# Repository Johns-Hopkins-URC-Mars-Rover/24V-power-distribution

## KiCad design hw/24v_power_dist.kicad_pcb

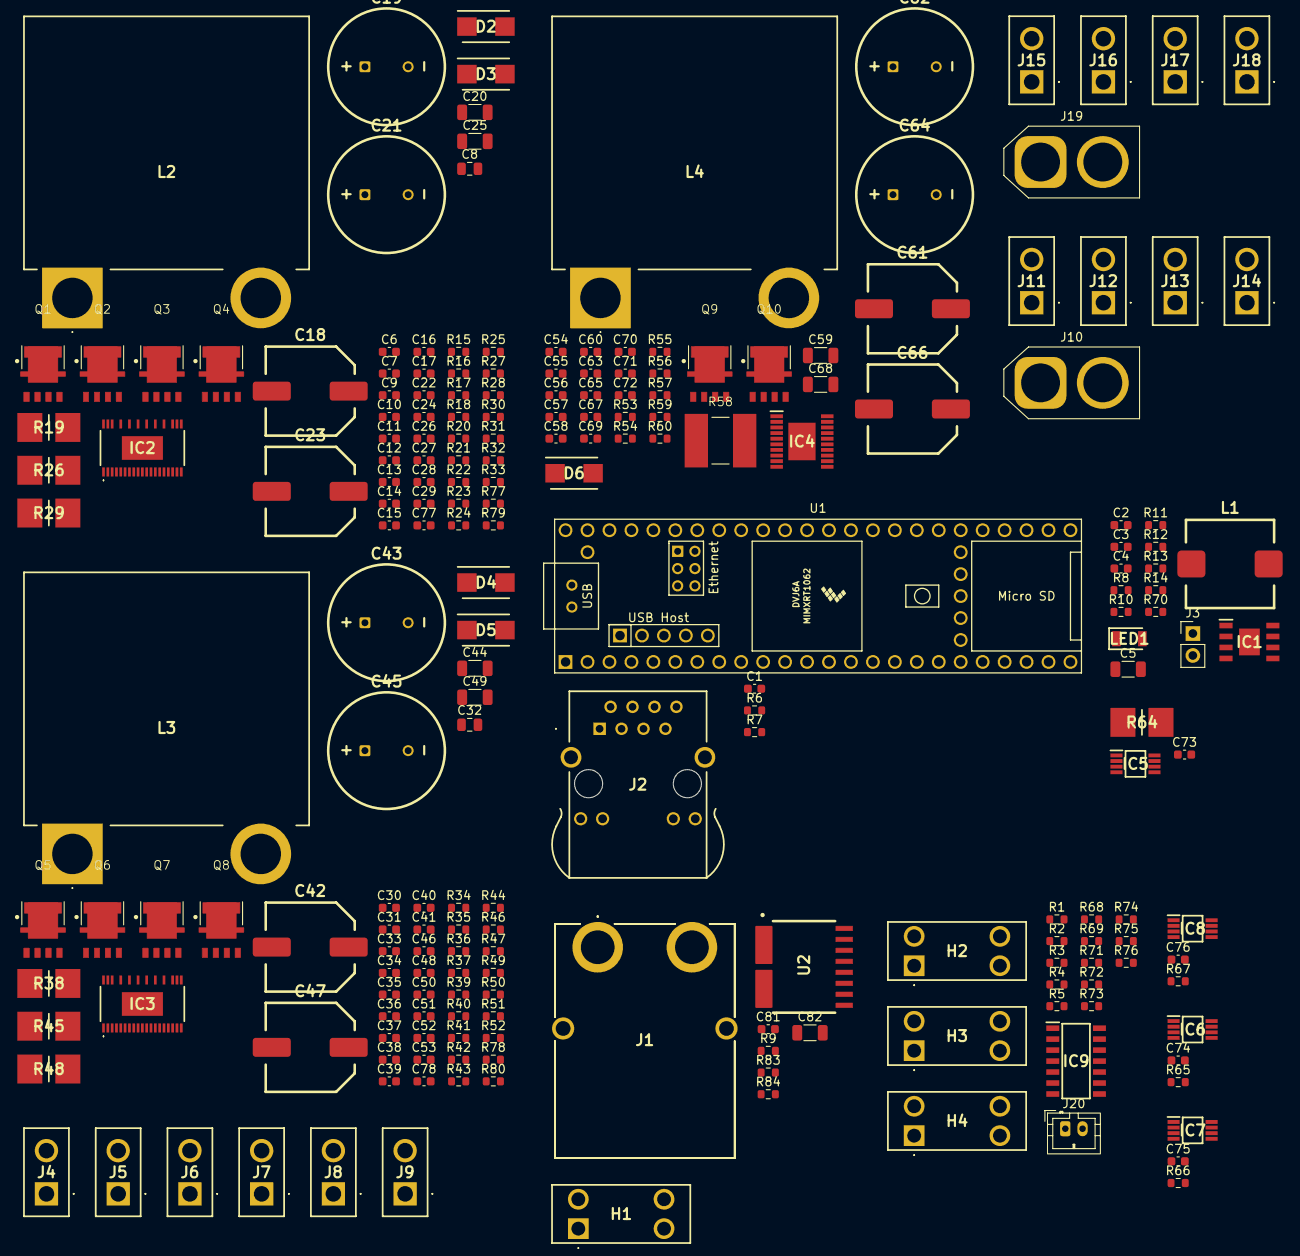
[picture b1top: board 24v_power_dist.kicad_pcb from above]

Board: 2 copper layers, 214 parts (0 on the bottom side), 130 nets, no tracks yet.

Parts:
C1, C3, C4, C26, C29, C50, C53, C56, C58, C69, C72, C73, C81: .1u; C_0603_1608Metric
C2, C13, C15, C37, C39, C77, C78: 4.7u; C_0603_1608Metric
C5, C20, C25, C44, C49, C68, C82: 10u; C_1206_3216Metric
C6, C10, C22, C27, C30, C34, C46, C51, C55, C65, C70: 1u; C_0603_1608Metric
C7, C31: 3.3n; C_0603_1608Metric
C8, C32: 330p; C_0805_2012Metric
C9, C11, C33, C35: 15.5n; C_0603_1608Metric
C12, C17, C24, C28, C36, C41, C48, C52, C67, C71: .47u; C_0603_1608Metric
C14, C16, C38, C40: 1n; C_0603_1608Metric
C18, C23, C42, C47, C61, C66: 150u; A786MW157M1JLAS011
C19, C21, C43, C45, C62, C64: 1m; ESY108M035AL4AA
C54: 100p; C_0603_1608Metric
C57: 390p; C_0603_1608Metric
C59: 10p; C_1206_3216Metric
C60: 120p; C_0603_1608Metric
C63: 10u; C_0603_1608Metric
C74, C75, C76: .01u; C_0603_1608Metric
D2, D3, D4, D5, D6: MBRS1100T3G; MBRS1100
H1, H2, H3, H4: 3568-10; 356810
IC1: LMR38010SQDDARQ1
IC2, IC3: LT8705HFE#PBF; LT8705HFEPBF
IC4: LM5116MHX_NOPB; LM5116MHXNOPB
IC5: INA282AIDGKR
IC6, IC7, IC8: TMP1075DGKR
IC9: MCP6004-I_SL; MCP6004
J1: XT90PW-M; XT90PWM
J2: HFJ11-2450E-L12RL; HFJ112450EL12RL
J3: Conn_01x02; PinHeader_1x02_P2.54mm_Vertical
J4, J5, J6, J7, J8, J9, J11, J12, J13, J14, J15, J16, J17, J18: XT30UPB-F; XT30UPBF
J10, J19: XT60PB-F; AMASS_XT60-F_1x02_P7.20mm_Vertical
J20: Conn_01x02; JST_PH_B2B-PH-K_1x02_P2.00mm_Vertical
L1: 10u; IHLP4040DZEE100M01
L2, L3, L4: B82559A5602A033
LED1: LTST-C150KFKT; LEDC3216X120N
Q1, Q2, Q3, Q4, Q5, Q6, Q7, Q8, Q9, Q10: NTMYS3D3N06CLTWG
R1, R2, R3, R4, R5, R9, R65, R66, R67: 5k; R_0603_1608Metric
R6, R7: 200; R_0603_1608Metric
R8, R13, R15, R34: 100k; R_0603_1608Metric
R10, R11, R83: 12k; R_0603_1608Metric
R12: 150; R_0603_1608Metric
R14: 24.9k; R_0603_1608Metric
R16, R35, R60: 8.2k; R_0603_1608Metric
R17, R36: 58k; R_0603_1608Metric
R18, R22, R31, R37, R41, R50, R57, R68, R71, R73, R75: 10k; R_0603_1608Metric
R19, R26, R29, R38, R45, R48, R64: 580070763021; RESC6331X58N
R20, R21, R23, R24, R39, R40, R42, R43: 2; R_0603_1608Metric
R25, R28, R44, R47: 10; R_0603_1608Metric
R27, R46: 4.3; R_0603_1608Metric
R30, R49: 190k; R_0603_1608Metric
R32, R33, R51, R52, R54, R77, R78, R79, R80: 0; R_0603_1608Metric
R53: 100K; R_0603_1608Metric
R55: 6.8k; R_0603_1608Metric
R56: 430; R_0603_1608Metric
R58: 3m; SVSQ392050R003FTDG
R59: 150k; R_0603_1608Metric
R69, R72, R74, R76: 82k; R_0603_1608Metric
R70: 1.5k; R_0603_1608Metric
R84: 29k; R_0603_1608Metric
U1: Teensy4.1; Teensy41
U2: TMCS1126C2AQDVGRQ1

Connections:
/3v3_teensy: C81.1, C82.1, IC9.4 (VDD), R1.1, R2.1, R3.2, R4.2, R5.2, R6.2, R7.1, R9.1, R65.1, R66.1, R67.1, R84.2, U1.46 (3V3), U2.4 (VS)
/5V_AUX: C5.1, C73.1, C74.1, C75.1, C76.1, IC5.6 (V+), IC6.8 (V+), IC7.8 (V+), IC8.8 (V+), R13.2, U1.48 (VIN)
/5V_AUX/BOOT: C4.1, IC1.7 (BOOT)
/5V_AUX/FB: IC1.5 (FB), R13.1, R14.2
/5V_AUX/SW: C4.2, IC1.8 (SW), L1.1
/5V_AUX/SYNC: IC1.4 (RT/SYNC), R70.2
/12V_Buck/CAPIN: C56.1, C61.1, C63.1, C65.1, C67.1, C69.1, IC4.20 (SW), L4.1, Q9.1 (S), Q9.2 (S), Q9.3 (S), Q10.5 (D)
/12V_Buck/COMP: C59.2, IC4.9 (COMP)
/12V_Buck/CS: IC4.12 (CS), Q10.1 (S), Q10.2 (S), Q10.3 (S), R58.1
/12V_Buck/EN_BUCK: IC4.4 (EN), R53.1, U1.28 (36_CS)
/12V_Buck/FB: C59.1, C60.1, IC4.8 (FB)
/12V_Buck/HB: C56.2, D6.1 (K), IC4.18 (HB)
/12V_Buck/HO: IC4.19 (HO), Q9.4 (G)
/12V_Buck/LO: IC4.15 (LO), Q10.4 (G)
/12V_Buck/RAMP: C57.1, IC4.5 (RAMP)
/12V_Buck/SS: C58.1, IC4.7 (SS)
/12V_Buck/SYNC: C54.1, IC3.13 (CLKOUT), IC4.3 (RT/SYNC), R54.1, R54.2, R55.1
/12V_Buck/UVLO: IC4.2 (UVLO), R59.2, R60.1
/12V_Buck/VCC: C55.1, D6.2 (A), IC4.16 (VCC)
/12V_Buck/VIN: C2.1, C3.1, C10.1, C18.1, C20.1, C22.1, C24.1, C26.1, C34.1, C42.1, C44.1, C46.1, C48.1, C50.1, IC1.3 (VIN), IC2.38 (VIN), IC3.38 (VIN), IC4.1 (VIN), J3.1, Q9.5 (D), R19.1, R38.1, R59.1, R73.1, R77.1, R78.1, U2.2 (IN-)
/12V_CUR: C62.1, C64.1, C66.1, C68.1, C70.1, C71.1, C72.1, IC4.10 (VOUT), IC5.1 (-IN), L4.2, R64.1
/12V_IM: IC5.5 (OUT), U1.39 (17_A3_TX4_SDA1)
/12V_OUT: H2.3 (B), H2.4 (B), J4.1 (Pos), J5.1 (Pos), J6.1 (Pos), J7.1 (Pos), J8.1 (Pos), J9.1 (Pos), R75.1
/24V_A: H4.3 (B), H4.4 (B), J15.1 (Pos), J16.1 (Pos), J17.1 (Pos), J18.1 (Pos), J19.1 (+), R68.1
/24V_B: H3.3 (B), H3.4 (B), J10.1 (+), J11.1 (Pos), J12.1 (Pos), J13.1 (Pos), J14.1 (Pos), R71.1
/Battery Input/OC_n: R9.2, U1.25 (33_MCLK2), U2.3 (OC_n)
/Battery Input/VOC: R83.2, R84.1, U2.5 (VOC)
/Battery Input/VOUT: U1.33 (41_A17), U2.6 (VOUT)
/Battery Input/VREF: U1.32 (40_A16), U2.7 (VREF)
/Buck Boost Chan A/BG1: Q2.4 (G), R20.2
/Buck Boost Chan A/BG2: Q3.4 (G), R21.2
/Buck Boost Chan A/BOOST1: C12.1, D2.1 (K), IC2.28 (BOOST1)
/Buck Boost Chan A/BOOST2: C17.1, D3.1 (K), IC2.20 (BOOST2)
/Buck Boost Chan A/CAPOUT: C19.1, C21.1, C23.1, C25.1, C27.1, C28.1, C29.1, IC2.30 (EXTVCC), Q4.5 (D), R29.1, R79.1
/Buck Boost Chan A/CSN: C16.2, IC2.5 (CSN), R28.2
/Buck Boost Chan A/CSNIN: IC2.36 (CSNIN), Q1.5 (D), R19.2, R33.2
/Buck Boost Chan A/CSNOUT: H4.1 (A), H4.2 (A), IC2.32 (CSNOUT), R29.2, R30.1, R32.2
/Buck Boost Chan A/CSP: C14.1, IC2.6 (CSP), R25.1
/Buck Boost Chan A/CSPIN: IC2.37 (CSPIN), R33.1, R77.2
/Buck Boost Chan A/CSPOUT: IC2.34 (CSPOUT), R32.1, R79.2
/Buck Boost Chan A/FBOUT: IC2.9 (FBOUT), R30.2, R31.1
/Buck Boost Chan A/GATEVCC: C13.2, C15.2, IC2.1 (INTVCC), IC2.18 (GATEVCC), R27.1
/Buck Boost Chan A/IMON_IN: C9.1, IC2.3 (IMON_IN), R18.1, U1.45 (23_A9_CRX1_MCLK1)
/Buck Boost Chan A/IMON_OUT: C11.1, IC2.10 (IMON_OUT), R22.1, U1.44 (22_A8_CTX1)
/Buck Boost Chan A/RT: IC2.15 (RT), R16.2
/Buck Boost Chan A/SHDN_n: IC2.4 (~SHDN), U1.30 (38_CS1_IN1)
/Buck Boost Chan A/SW1: C12.2, IC2.24 (SW1), L2.1, Q1.1 (S), Q1.2 (S), Q1.3 (S), Q2.5 (D)
/Buck Boost Chan A/SW2: C17.2, IC2.22 (SW2), L2.2, Q3.5 (D), Q4.1 (S), Q4.2 (S), Q4.3 (S)
/Buck Boost Chan A/TG1: Q1.4 (G), R24.2
/Buck Boost Chan A/TG2: Q4.4 (G), R23.2
/Buck Boost Chan A/VC: C8.2, IC2.11 (VC), R17.2
/Buck Boost Chan B/BG1: Q6.4 (G), R39.2
/Buck Boost Chan B/BG2: Q7.4 (G), R40.2
/Buck Boost Chan B/BOOST1: C36.1, D4.1 (K), IC3.28 (BOOST1)
/Buck Boost Chan B/BOOST2: C41.1, D5.1 (K), IC3.20 (BOOST2)
/Buck Boost Chan B/CAPOUT: C43.1, C45.1, C47.1, C49.1, C51.1, C52.1, C53.1, IC3.30 (EXTVCC), Q8.5 (D), R48.1, R80.1
/Buck Boost Chan B/CSN: C40.2, IC3.5 (CSN), R47.2
/Buck Boost Chan B/CSNIN: IC3.36 (CSNIN), Q5.5 (D), R38.2, R52.2
/Buck Boost Chan B/CSNOUT: H3.1 (A), H3.2 (A), IC3.32 (CSNOUT), R48.2, R49.1, R51.2
/Buck Boost Chan B/CSP: C38.1, IC3.6 (CSP), R44.1
/Buck Boost Chan B/CSPIN: IC3.37 (CSPIN), R52.1, R78.2
/Buck Boost Chan B/CSPOUT: IC3.34 (CSPOUT), R51.1, R80.2
/Buck Boost Chan B/FBOUT: IC3.9 (FBOUT), R49.2, R50.1
/Buck Boost Chan B/GATEVCC: C37.2, C39.2, IC3.1 (INTVCC), IC3.18 (GATEVCC), R46.1
/Buck Boost Chan B/IMON_IN: C33.1, IC3.3 (IMON_IN), R37.1, U1.43 (21_A7_RX5_BCLK1)
/Buck Boost Chan B/IMON_OUT: C35.1, IC3.10 (IMON_OUT), R41.1, U1.42 (20_A6_TX5_LRCLK1)
/Buck Boost Chan B/RT: IC3.15 (RT), R35.2
/Buck Boost Chan B/SHDN_n: IC3.4 (~SHDN), U1.29 (37_CS)
/Buck Boost Chan B/SW1: C36.2, IC3.24 (SW1), L3.1, Q5.1 (S), Q5.2 (S), Q5.3 (S), Q6.5 (D)
/Buck Boost Chan B/SW2: C41.2, IC3.22 (SW2), L3.2, Q7.5 (D), Q8.1 (S), Q8.2 (S), Q8.3 (S)
/Buck Boost Chan B/TG1: Q5.4 (G), R43.2
/Buck Boost Chan B/TG2: Q8.4 (G), R42.2
/Buck Boost Chan B/VC: C32.2, IC3.11 (VC), R36.2
/Current Sense/VOUT: H2.1 (A), H2.2 (A), IC5.8 (+IN), R64.2
/TEMP_12V: IC7.3 (ALERT), R66.2, U1.31 (39_MISO1_OUT1A)
/TEMP_24A: IC6.3 (ALERT), R65.2, U1.27 (35_TX8)
/TEMP_24B: IC8.3 (ALERT), R67.2, U1.26 (34_RX8)
/Teensy4.1/R+: J2.3 (RD+), U1.60 (R+)
/Teensy4.1/R-: J2.6 (RD-), U1.65 (R-)
/Teensy4.1/SCL: IC6.2 (SCL), IC7.2 (SCL), IC8.2 (SCL), R1.2, U1.16 (24_A10_TX6_SCL2)
/Teensy4.1/SDA: IC6.1 (SDA), IC7.1 (SDA), IC8.1 (SDA), R2.2, U1.17 (25_A11_RX6_SDA2)
/Teensy4.1/T+: J2.1 (TD+), U1.63 (T+)
/Teensy4.1/T-: J2.2 (TD-), U1.62 (T-)
/Temp Sense1/A0: IC7.7 (A0), R3.1
/Temp Sense2/A0: IC8.7 (A0), R4.1
/Temp Sense2/A1: IC8.6 (A1), R5.1
/VMEAS_12V: IC9.8 (VOUT_C), IC9.9 (VINC-), U1.38 (16_A2_RX4_SCL1)
/VMEAS_24V_A: IC9.1 (VOUTA), IC9.2 (VINA-), U1.41 (19_A5_SCL)
/VMEAS_24V_B: IC9.6 (VINB-), IC9.7 (VOUT_B), U1.40 (18_A4_SDA)
/VMEAS_BATT: IC9.13 (VIND-), IC9.14 (VOUTD), U1.37 (15_A1_RX3_SPDIF_IN)
GND: C1.1, C2.2, C3.2, C5.2, C6.1, C7.1, C8.1, C9.2, C10.2, C11.2, C13.1, C14.2, C15.1, C16.1, C18.2, C19.2, C20.2, C21.2, C22.2, C23.2, C24.2, C25.2, C26.2, C27.2, C28.2, C29.2, C30.1, C31.1, C32.1, C33.2, C34.2, C35.2, C37.1, C38.2, C39.1, C40.1, C42.2, C43.2, C44.2, C45.2, C46.2, C47.2, C48.2, C49.2, C50.2, C51.2, C52.2, C53.2, C54.2, C55.2, C57.2, C58.2, C61.2, C62.2, C63.2, C64.2, C65.2, C66.2, C67.2, C68.2, C69.2, C70.2, C71.2, C72.2, C73.2, C74.2, C75.2, C76.2, C77.1, C78.1, C81.2, C82.2, IC1.1 (GND), IC1.9 (EP), IC2.2 (MODE), IC2.14 (SYNC), IC2.16 (GND_1), IC2.39 (GND_2), IC3.2 (MODE), IC3.14 (SYNC), IC3.16 (GND_1), IC3.39 (GND_2), IC4.6 (AGND), IC4.13 (CSG), IC4.14 (PGND), IC4.17 (VCCX), IC4.21 (EP), IC5.2 (GND), IC5.3 (REF2), IC5.7 (REF1), IC6.4 (GND), IC6.5 (A2), IC6.6 (A1), IC6.7 (A0), IC7.4 (GND), IC7.5 (A2), IC7.6 (A1), IC8.4 (GND), IC8.5 (A2), IC9.11 (VSS), J1.2 (Neg), J1.MH1, J1.MH2, J2.8 (GND), J2.10 (K_GREEN), J2.12 (K_YELLOW), J2.13 (SHIELD_1), J2.14 (SHIELD_2), J4.2 (Neg), J5.2 (Neg), J6.2 (Neg), J7.2 (Neg), J8.2 (Neg), J9.2 (Neg), J10.2 (-), J11.2 (Neg), J12.2 (Neg), J13.2 (Neg), J14.2 (Neg), J15.2 (Neg), J16.2 (Neg), J17.2 (Neg), J18.2 (Neg), J19.2 (-), R8.2, R11.1, R14.1, R15.1, R18.2, R22.2, R31.2, R34.1, R37.2, R41.2, R50.2, R53.2, R56.2, R57.2, R58.2, R60.2, R69.2, R72.2, R74.2, R76.2, R83.1, U1.1 (GND), U1.34 (GND), U1.47 (GND), U1.52 (GND), U1.58 (GND), U1.59 (GND), U1.64 (GND), U2.9 (GND)
unnamed: C7.2, R17.1
unnamed: C31.2, R36.1
unnamed: L1.2, LED1.2
unnamed: D2.2 (A), D3.2 (A), R27.2
unnamed: D4.2 (A), D5.2 (A), R46.2
unnamed: IC1.2 (EN), J3.2, R8.1
unnamed: IC1.6 (PG), R12.1
unnamed: IC2.17 (BG1), R20.1
unnamed: IC2.19 (BG2), R21.1
unnamed: C77.2, IC2.7 (LDO33), IC2.8 (FBIN)
unnamed: C6.2, IC2.12 (SS)
unnamed: IC2.26 (TG1), R24.1
unnamed: IC2.21 (TG2), R23.1
unnamed: IC3.17 (BG1), R39.1
unnamed: IC3.19 (BG2), R40.1
unnamed: C78.2, IC3.7 (LDO33), IC3.8 (FBIN)
unnamed: C30.2, IC3.12 (SS)
unnamed: IC3.26 (TG1), R43.1
unnamed: IC3.21 (TG2), R42.1
unnamed: IC4.11 (DEMB), R57.1
unnamed: IC9.3 (VINA+), R68.2, R69.1
unnamed: IC9.5 (VINB+), R71.2, R72.1
unnamed: IC9.10 (VINC+), R75.2, R76.1
unnamed: IC9.12 (VIND+), R73.2, R74.1
unnamed: H1.1 (A), H1.2 (A), J1.1 (Pos)
unnamed: J2.9 (A_GREEN), R6.1
unnamed: J2.11 (A_YELLOW), R7.2
unnamed: C1.2, J2.4 (CT_1), J2.5 (CT_2)
unnamed: LED1.1, R12.2
unnamed: Q2.1 (S), Q2.2 (S), Q2.3 (S), Q3.1 (S), Q3.2 (S), Q3.3 (S), R25.2, R26.1
unnamed: Q6.1 (S), Q6.2 (S), Q6.3 (S), Q7.1 (S), Q7.2 (S), Q7.3 (S), R44.2, R45.1
unnamed: R10.1, R11.2
unnamed: R10.2, R70.1
unnamed: R15.2, R16.1
unnamed: R26.2, R28.1
unnamed: R34.2, R35.1
unnamed: R45.2, R47.1
unnamed: R55.2, R56.1
unnamed: H1.3 (B), H1.4 (B), U2.1 (IN+)
